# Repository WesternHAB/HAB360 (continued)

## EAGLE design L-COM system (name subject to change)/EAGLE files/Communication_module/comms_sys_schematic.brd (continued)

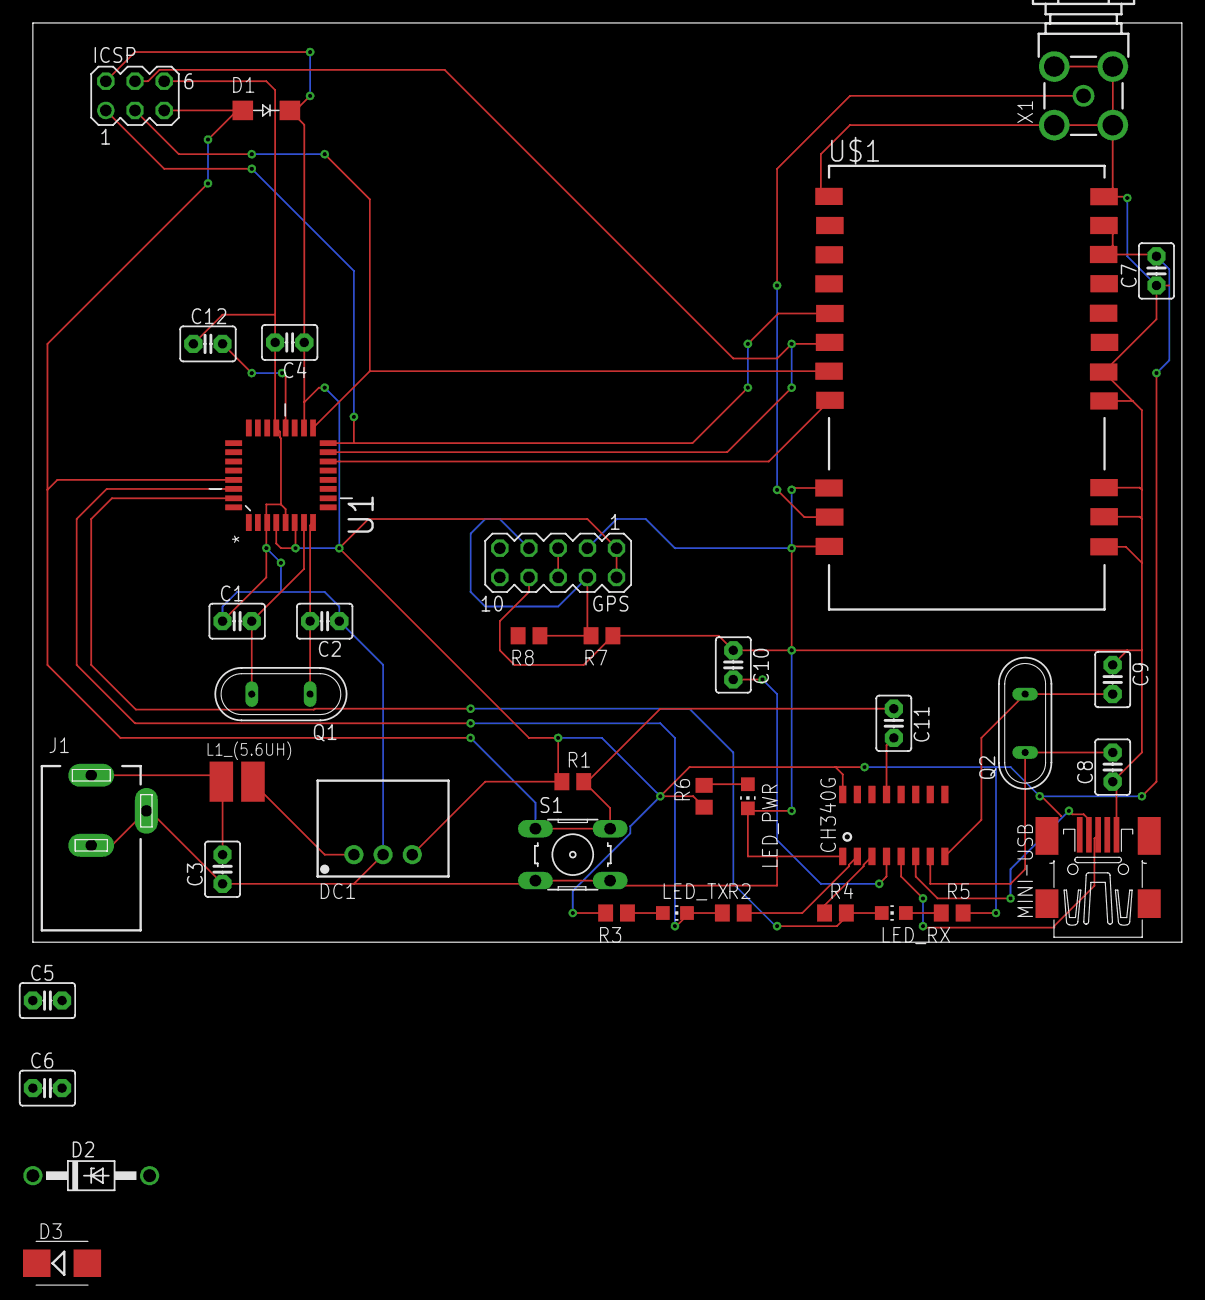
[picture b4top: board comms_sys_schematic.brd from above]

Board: 2 copper layers, 100.0 x 80.0 mm, 39 parts (0 on the bottom side), 29 nets.

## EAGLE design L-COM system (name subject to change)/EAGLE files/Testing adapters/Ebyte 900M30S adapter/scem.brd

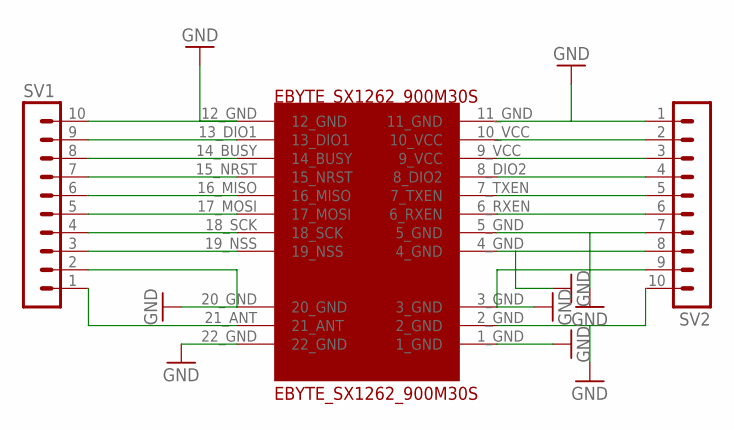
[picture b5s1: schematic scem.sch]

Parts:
EBYTE_SX1262_900M30S: EBYTE_SX1262_900M30S; EBYTE_SX1262_900M30S_FOOTPRINT
SV1, SV2: MA10-1

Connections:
GND: EBYTE_SX1262_900M30S.1_GND, EBYTE_SX1262_900M30S.2_GND, EBYTE_SX1262_900M30S.3_GND, EBYTE_SX1262_900M30S.4_GND, EBYTE_SX1262_900M30S.5_GND, EBYTE_SX1262_900M30S.11_GND, EBYTE_SX1262_900M30S.12_GND, EBYTE_SX1262_900M30S.20_GND, EBYTE_SX1262_900M30S.22_GND, SV1.2, SV1.10, SV2.1, SV2.7, SV2.8, SV2.9, SV2.10
unnamed: EBYTE_SX1262_900M30S.13_DIO1, SV1.9
unnamed: EBYTE_SX1262_900M30S.14_BUSY, SV1.8
unnamed: EBYTE_SX1262_900M30S.15_NRST, SV1.7
unnamed: EBYTE_SX1262_900M30S.16_MISO, SV1.6
unnamed: EBYTE_SX1262_900M30S.17_MOSI, SV1.5
unnamed: EBYTE_SX1262_900M30S.18_SCK, SV1.4
unnamed: EBYTE_SX1262_900M30S.19_NSS, SV1.3
unnamed: EBYTE_SX1262_900M30S.21_ANT, SV1.1
unnamed: EBYTE_SX1262_900M30S.10_VCC, SV2.2
unnamed: EBYTE_SX1262_900M30S.9_VCC, SV2.3
unnamed: EBYTE_SX1262_900M30S.8_DIO2, SV2.4
unnamed: EBYTE_SX1262_900M30S.7_TXEN, SV2.5
unnamed: EBYTE_SX1262_900M30S.6_RXEN, SV2.6

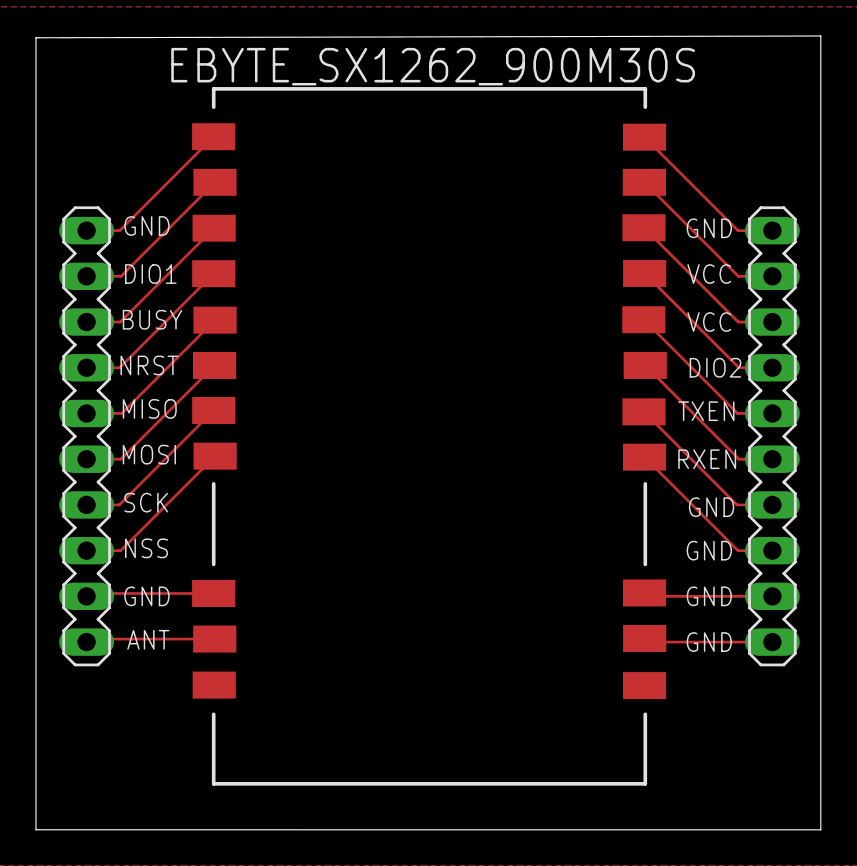
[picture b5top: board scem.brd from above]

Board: 2 copper layers, 43.6 x 44.1 mm, 3 parts (0 on the bottom side), 14 nets.

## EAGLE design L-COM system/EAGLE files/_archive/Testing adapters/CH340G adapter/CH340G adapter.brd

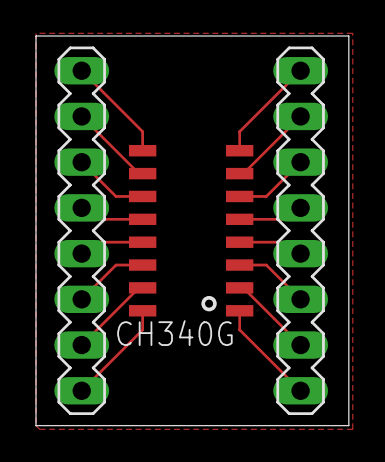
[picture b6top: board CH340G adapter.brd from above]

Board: 2 copper layers, 17.4 x 21.6 mm, 3 parts (0 on the bottom side), 16 nets.

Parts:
SV1, SV2: MA08-1
U$1: CH340G; SOIC16

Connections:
unnamed: SV1.8, U$1.1
unnamed: SV1.7, U$1.2
unnamed: SV1.6, U$1.3
unnamed: SV1.5, U$1.4
unnamed: SV1.4, U$1.5
unnamed: SV1.3, U$1.6
unnamed: SV1.2, U$1.7
unnamed: SV1.1, U$1.8
unnamed: SV2.8, U$1.9
unnamed: SV2.7, U$1.10
unnamed: SV2.6, U$1.11
unnamed: SV2.5, U$1.12
unnamed: SV2.4, U$1.13
unnamed: SV2.3, U$1.14
unnamed: SV2.2, U$1.15
unnamed: SV2.1, U$1.16

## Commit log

2020-06-25 L-COM and power system notes/files
2020-08-26 New files - small errors
    NOTE: in the schematic, the UART interface to the ATMEGA328 UART pins is wrong.
    The molex Tx should voltage divide to the 3.3V Rx of the ATMEGA, and a pull-up resistor + LED on the 3.3V segment
    The ATMEGA Tx should pass through a 1K current-limiting resistor to the Molex Rx (no voltage division needed). A pull-up resistor and LED should be on the segment of wire between the ATMEGA and 1K re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
    The parts list does not accurately reflect the current state and needs to be updated.
2020-10-02 Updated board design
    Reddit gave some reccomendations
2020-10-08 Touch-ups to board
    Small changes to the board, namely ensuring the antenna trace is properly designed (40 mil width for antenna-matching 50-Ohm impedance, via fence, removal of thermal reliefs on SMA connector).
2020-10-22 Various improvements/corrections
    Posted on Reddit, applied reccomendations
2020-10-22 Added readme to LCOM
2020-10-23 Small fixes to board. Created parts list
    Still need to source resistors, capacitors, fuses, etc.
    Some of the components may be sourced from elsewhere for a lot cheaper, but this list keeps it all in Digikey.
2020-10-30 V1 design finished, full parts list
    First version finished, complete parts list put together.
    Boards currently ordered from PCBWay to try out the design.
2020-11-26 Moving files
    Moved all desktop work into the repo so its not in two places.
2020-11-26 Replaced footprints for tantalum capacitors
    Swapped out the tantalum capacitor's footprints for a slightly different one. Includes polarity marking on silkscreen.
2020-12-08 Small change to screws
    Modified them to 2.2mm in diameter. Seems the fab house changed them from 3mm to 2.2mm in the order, which actually worked out better for fitting screws in.
    The 'top-left' screw (between pin header and ICSP header) was moved 0.3mm to the right to allow more of the ground plane to connect. Will be reflected in the 3D model of the casing.
2020-12-29 Board images, directory renamed
    Images of the first two (one working, the other mostly working) boards. Renamed directory because I don't want to bother thinking of another name for it at this point.
2021-02-04 LCOM-V2 update
    Updated to V2 of the board. Solved remaining outstanding issues (and hopefully did not introduce new ones).
    -Switched the DIO1 of EBYTE module to connected to interrupt pin PD2 of the ATMEGA.
    -Switched EBYTE rx/tx pins to PD6 and PD7 of ATMEGA.
    -Added an optional connection (by adding 0R resistor) to DIO2 of EBYTE.
    -Spaced ground plane from Vin traces to prevent arcing.
    -Moved C1 and C2 to backside, repositioned L1 to allow for cleaning around it.
2021-09-27 Software, documentation
2021-09-27 Removed old programs
2021-09-27 Forgot to actually upload the software
2021-09-27 Small formatting fix
2021-10-01 GUI fix, removed set COM port and allowed choice
